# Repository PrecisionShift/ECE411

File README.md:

# ECE411
Portland State University Practicum

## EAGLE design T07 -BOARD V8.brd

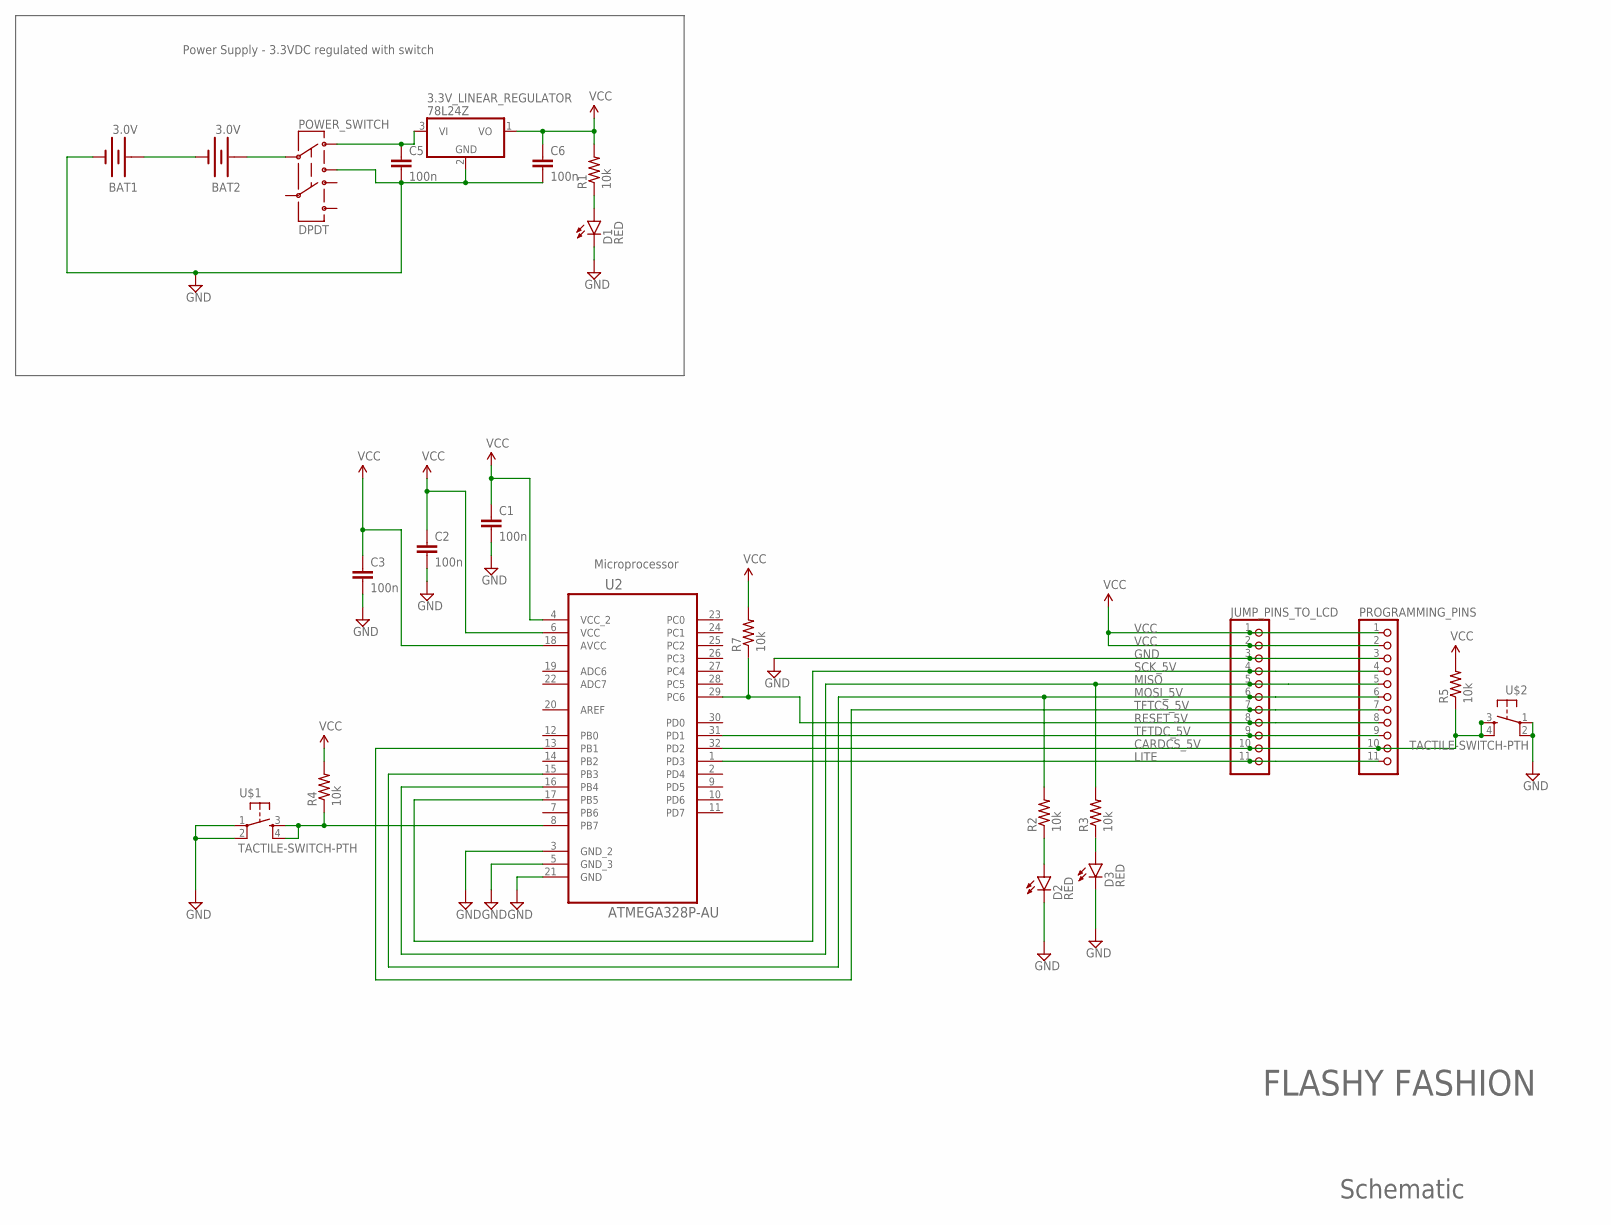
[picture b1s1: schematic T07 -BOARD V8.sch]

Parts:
3.3V_LINEAR_REGULATOR: 78L24Z; TO92
BAT1, BAT2: 3.0V; BATTCON_245MM_PTH
C1, C2, C3, C5, C6: 100n; 1206
D1, D2, D3: RED; LED-1206
JUMP_PINS_TO_LCD: HEADER-1X1176MIL; 1X11_ROUND_76
POWER_SWITCH: DPDT; AYZ0202
PROGRAMMING_PINS: HEADER-1X1176MIL; 1X11_ROUND_76
R1, R2, R3, R4, R5, R7: 10k; 1206
U2: ATMEGA328P-AU; QFP80P900X900X120-32N
U$1, U$2: TACTILE-SWITCH-PTH; TAC-SWITCH-PTH

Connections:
CARDCS_5V: JUMP_PINS_TO_LCD.10, PROGRAMMING_PINS.10, R5.1, U2.32 (PD2), U$2.3, U$2.4
GND: 3.3V_LINEAR_REGULATOR.2 (GND), BAT1.2 (-), C1.2, C2.2, C3.2, C5.2, C6.2, D1.C, D2.C, D3.C, JUMP_PINS_TO_LCD.3, POWER_SWITCH.3, PROGRAMMING_PINS.3, U2.3 (GND_2), U2.5 (GND_3), U2.21 (GND), U$1.1, U$1.2, U$2.1, U$2.2
LITE: JUMP_PINS_TO_LCD.11, PROGRAMMING_PINS.11, U2.1 (PD3)
MISO: JUMP_PINS_TO_LCD.5, PROGRAMMING_PINS.5, R3.2, U2.16 (PB4)
MOSI_5V: JUMP_PINS_TO_LCD.6, PROGRAMMING_PINS.6, R2.2, U2.15 (PB3)
unnamed: BAT1.3 (+), BAT2.2 (-)
unnamed: JUMP_PINS_TO_LCD.8, PROGRAMMING_PINS.8, R7.1, U2.29 (PC6)
unnamed: D1.A, R1.1
unnamed: R4.1, U2.8 (PB7), U$1.3, U$1.4
unnamed: BAT2.3 (+), POWER_SWITCH.2
unnamed: 3.3V_LINEAR_REGULATOR.3 (VI), C5.1, POWER_SWITCH.1
unnamed: D2.A, R2.1
unnamed: D3.A, R3.1
SCK_5V: JUMP_PINS_TO_LCD.4, PROGRAMMING_PINS.4, U2.17 (PB5)
TFTCS_5V: JUMP_PINS_TO_LCD.7, PROGRAMMING_PINS.7, U2.13 (PB1)
TFTDC_5V: JUMP_PINS_TO_LCD.9, PROGRAMMING_PINS.9, U2.31 (PD1)
VCC: 3.3V_LINEAR_REGULATOR.1 (VO), C1.1, C2.1, C3.1, C6.1, JUMP_PINS_TO_LCD.1, JUMP_PINS_TO_LCD.2, PROGRAMMING_PINS.1, PROGRAMMING_PINS.2, R1.2, R4.2, R5.2, R7.2, U2.4 (VCC_2), U2.6 (VCC), U2.18 (AVCC)

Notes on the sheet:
Power Supply - 3.3VDC regulated with switch
FLASHY FASHION
Microprocessor
Schematic
RESET 5V

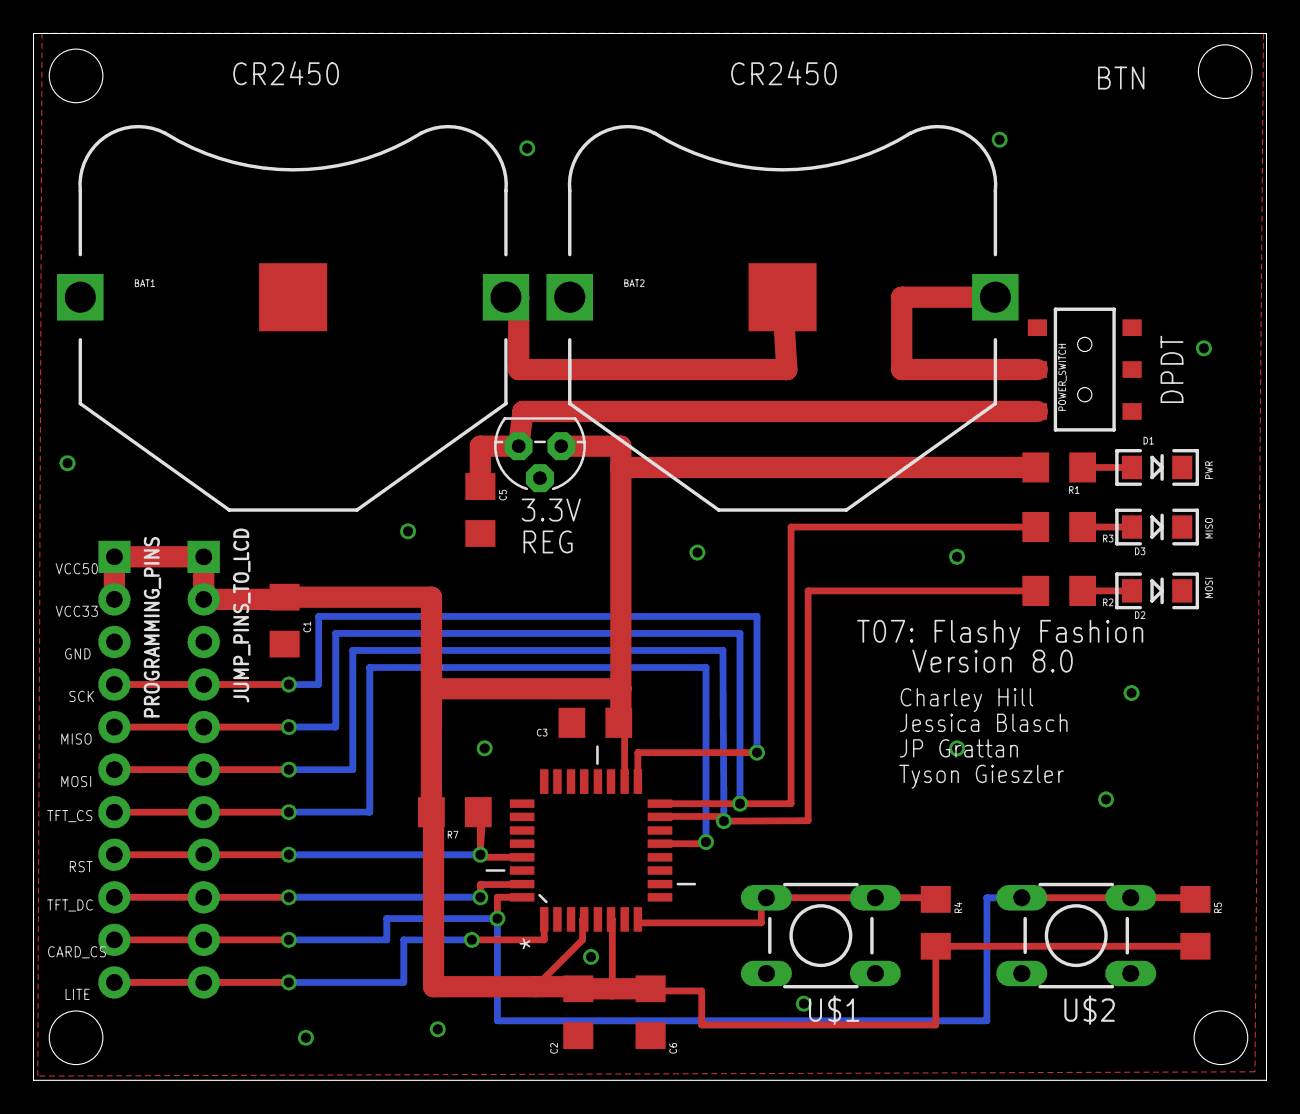
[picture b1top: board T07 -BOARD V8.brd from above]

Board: 2 copper layers, 73.6 x 62.5 mm, 23 parts (0 on the bottom side), 17 nets.

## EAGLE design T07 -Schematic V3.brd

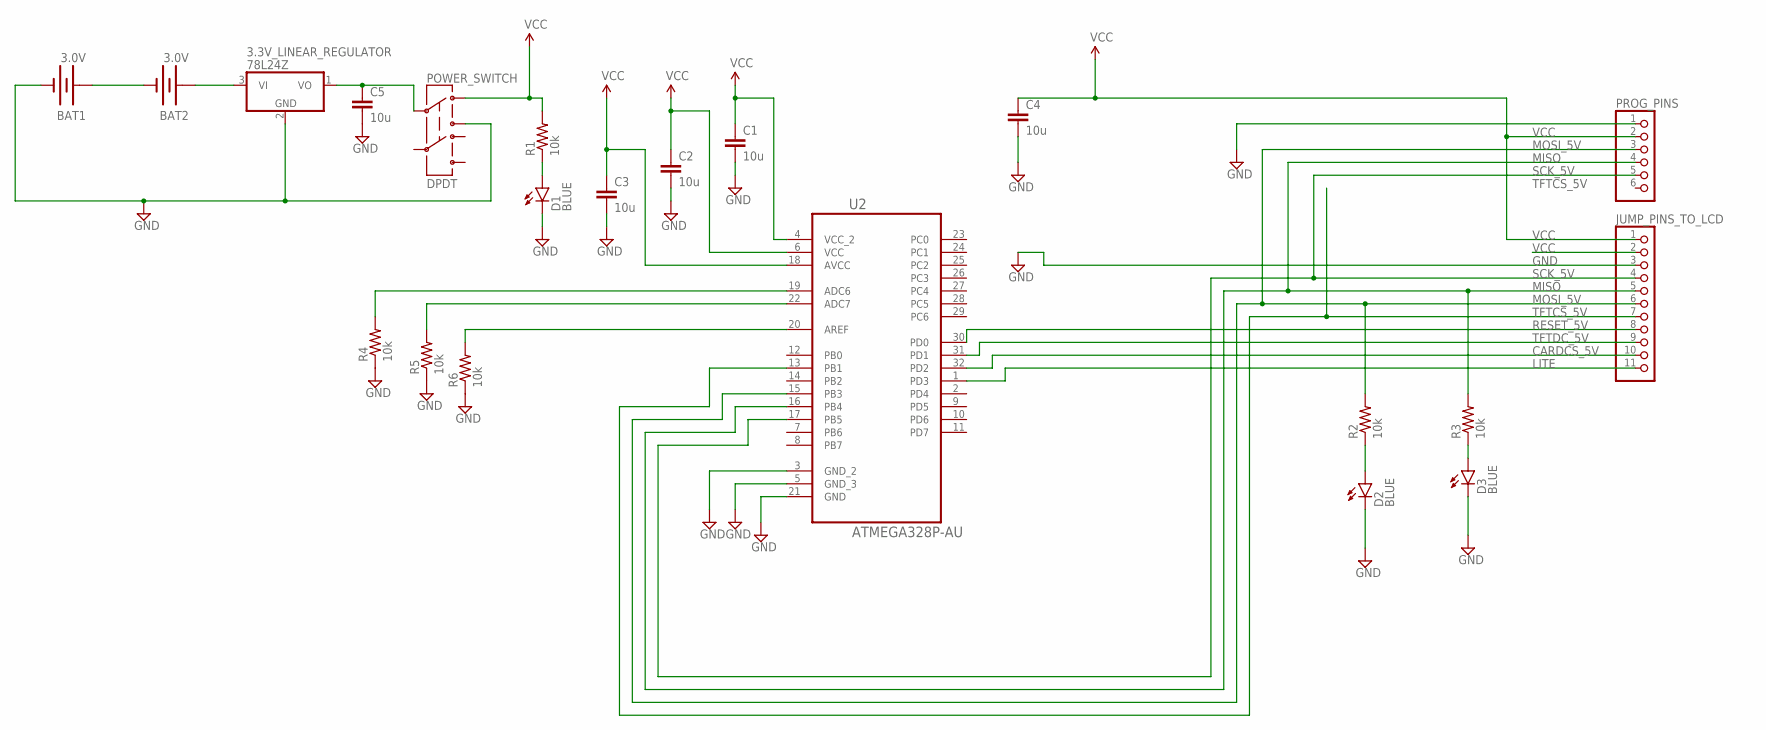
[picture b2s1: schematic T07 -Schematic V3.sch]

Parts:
3.3V_LINEAR_REGULATOR: 78L24Z; TO92
BAT1, BAT2: 3.0V; BATTCON_245MM_PTH
C1, C2, C3, C4, C5: 10u; 1206
D1, D2, D3: BLUE; LED-1206
JUMP_PINS_TO_LCD: HEADER-1X1176MIL; 1X11_ROUND_76
POWER_SWITCH: DPDT; AYZ0202
PROG_PINS: PINHD-1X6-3.5MM; 1X06-3.5MM
R1, R2, R3, R4, R5, R6: 10k; 1206
U2: ATMEGA328P-AU; QFP80P900X900X120-32N

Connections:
CARDCS_5V: JUMP_PINS_TO_LCD.10, U2.32 (PD2)
GND: 3.3V_LINEAR_REGULATOR.2 (GND), BAT1.2 (-), C1.2, C2.2, C3.2, C4.2, C5.2, D1.C, D2.C, D3.C, JUMP_PINS_TO_LCD.3, POWER_SWITCH.3, PROG_PINS.1, R4.1, R5.1, R6.1, U2.3 (GND_2), U2.5 (GND_3), U2.21 (GND)
LITE: JUMP_PINS_TO_LCD.11, U2.1 (PD3)
MISO: JUMP_PINS_TO_LCD.5, PROG_PINS.4, R3.2, U2.16 (PB4)
MOSI_5V: JUMP_PINS_TO_LCD.6, PROG_PINS.3, R2.2, U2.15 (PB3)
unnamed: BAT1.3 (+), BAT2.2 (-)
unnamed: 3.3V_LINEAR_REGULATOR.3 (VI), BAT2.3 (+)
unnamed: D1.A, R1.1
unnamed: R4.2, U2.19 (ADC6)
unnamed: 3.3V_LINEAR_REGULATOR.1 (VO), C5.1, POWER_SWITCH.2
unnamed: D2.A, R2.1
unnamed: D3.A, R3.1
unnamed: R5.2, U2.22 (ADC7)
unnamed: R6.2, U2.20 (AREF)
RESET_5V: JUMP_PINS_TO_LCD.8, U2.30 (PD0)
SCK_5V: JUMP_PINS_TO_LCD.4, PROG_PINS.5, U2.17 (PB5)
TFTCS_5V: JUMP_PINS_TO_LCD.7, U2.13 (PB1)
TFTDC_5V: JUMP_PINS_TO_LCD.9, U2.31 (PD1)
VCC: C1.1, C2.1, C3.1, C4.1, JUMP_PINS_TO_LCD.1, POWER_SWITCH.1, PROG_PINS.2, R1.2, U2.4 (VCC_2), U2.6 (VCC), U2.18 (AVCC)

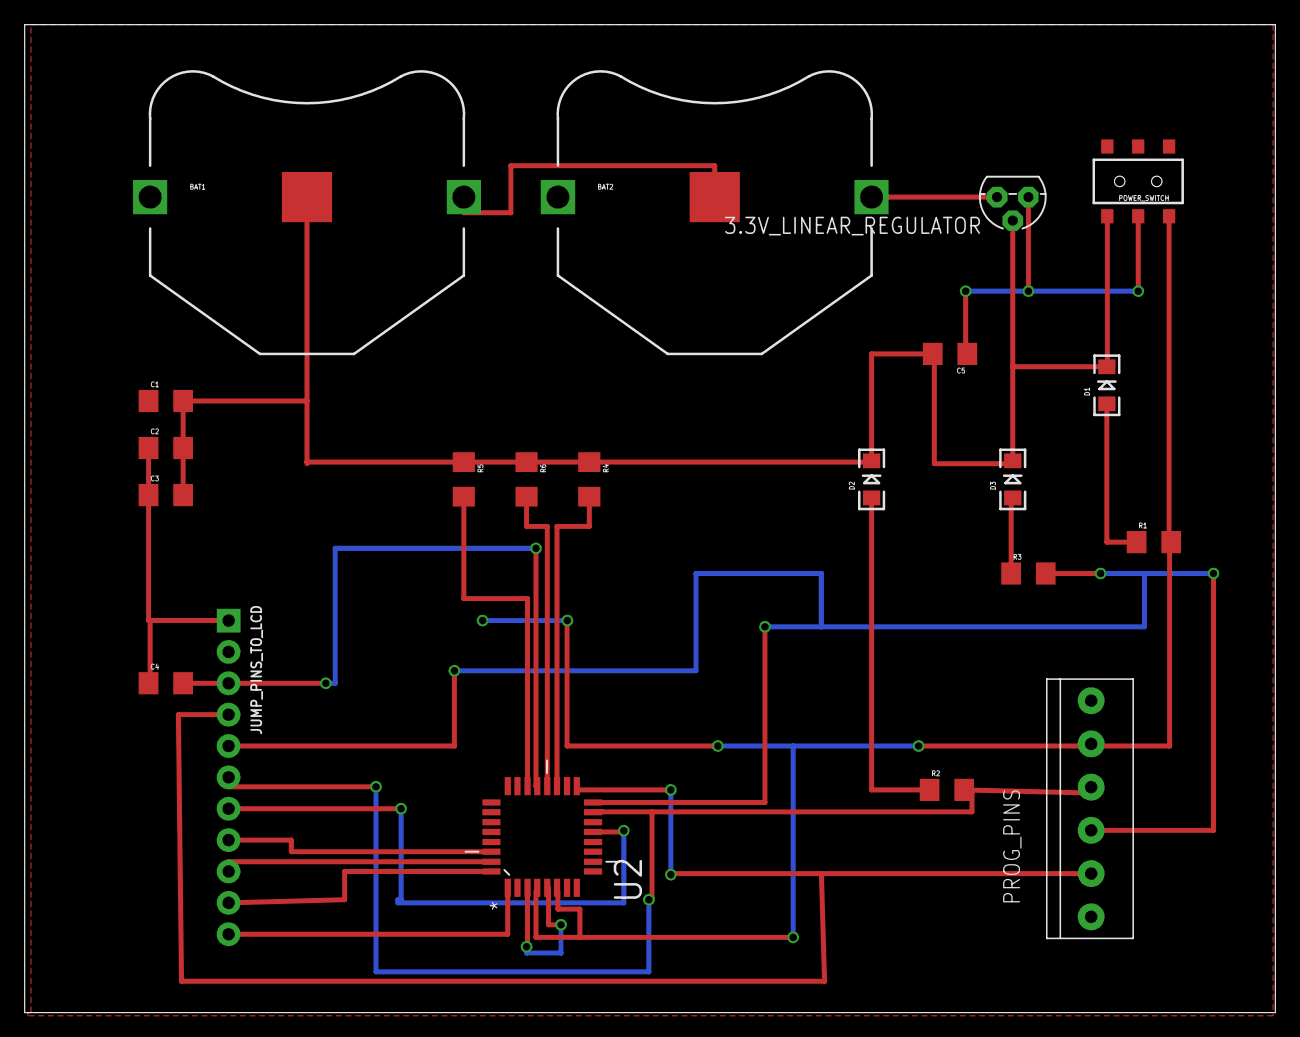
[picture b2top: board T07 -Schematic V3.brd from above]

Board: 2 copper layers, 101.3 x 80.0 mm, 21 parts (0 on the bottom side), 19 nets.

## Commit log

2016-10-10 Project Decision Matrix
2016-10-10 Project Decision Matrix .PNG
2016-10-16 Pinout Rev 16.10.1.0
    Description of what pins goes to what for each of the IC and Daughterboards
2016-10-19 Add files via upload
    Pinouts done over weekend 10/16.
2016-11-03 Rename Flash_Fashion Schematic.sch to T07-schematic.sch
2016-11-04 Rename Flash_Fashion Schematic.brd to T07-Layout.brd
2016-11-04 Rename T07-Layout.brd to T07-Schematic.brd
2016-11-04 Rename T07-schematic.sch to T07-Schematic.sch
2016-11-08 Rename T07-Schematic.brd to T07-Schematic V1.brd
2016-11-08 Rename T07-Schematic.sch to T07-Schematic V1.sch
2016-11-08 Add files via upload
    Added GND plane to front and fixed a connection issue on TFTCS.
2016-11-08 Rename Flash_Fashion Schematic V2.brd to T07-Schematic V2.brd
2016-11-08 Rename Flash_Fashion Schematic V2.sch to T07-Schematic V2.sch
2016-11-09 Add files via upload
    changed the Vcc connections on schematic. Rewired the same connection on the board. Also re-added GND plane to front of board.
2016-11-09 Add files via upload
    added frame and reconnected things that disappeared on board somehow.
2016-11-10 making things look correct
    deleting all the versions except for the latest one and progressing from there correctly.
2016-11-10 making things look correct
    deleting everything but the latest version to correct clutter and will continue to add files only using branch and commit from now on.
2016-11-10 changed the name of the file to be more obvious
    deleting everything but the latest version to correct clutter and will continue to add files only using branch and commit from now on.
2016-11-13 uploading new files
2016-11-13 uploading new files
    added button, condensed board moved coupling caps closer. added name in middle of board
2016-11-13 Rename T07 -Schematic V5.brd to T07 -Board V5.brd
    changed name of board file
2016-11-14 DisplayDriverOne
    Not Functional
2016-11-15 Add files via upload
    Team 07: ECE411 - Homework 5
2016-11-15 T07 - ECE411: hw5
2016-11-17 deleted to make room for newest revision
    i am uploading the final board right now.
2016-11-17 making room for a new board
    uploading the newest board
2016-11-17 these are the boards that got sent to OSH PARK
    look we forgot to remove the name part for the button and i didn't catch it during the upload
2016-11-20 not sure
2016-11-20 CleanUpAttempt
    Still doesn't work
2016-11-20 preBreak1:55pm11/20/2016
    not working confirmed spi output
2016-11-23 23nov16@1:44
    First functional display code
2016-11-24 T07-ECE411_hw6
2016-11-29 Mask Files V1
2016-11-30 twoImages1
    Two images are working but the button only goes one way.
2016-12-07 Deleting this to make room for revision
    the final revision (we think)
2016-12-07 Delete to make room for new revision
    the final revision
2016-12-07 added butons
    added buttons to the board layout and schematic. these are actually attached on the case and not the board but this allows everyone to know about them.
2016-12-08 added bill of materials and pic of bill of materials

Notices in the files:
parts and their libraries:
SparkFun-Electromechanical: Licensing: Creative Commons ShareAlike 4.0 International - https://creativecommons.org/licenses/by-sa/4.0
microbuilder: This work is placed in the public domain, and may be freely used for commercial and non-commercial work with the following conditions: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
